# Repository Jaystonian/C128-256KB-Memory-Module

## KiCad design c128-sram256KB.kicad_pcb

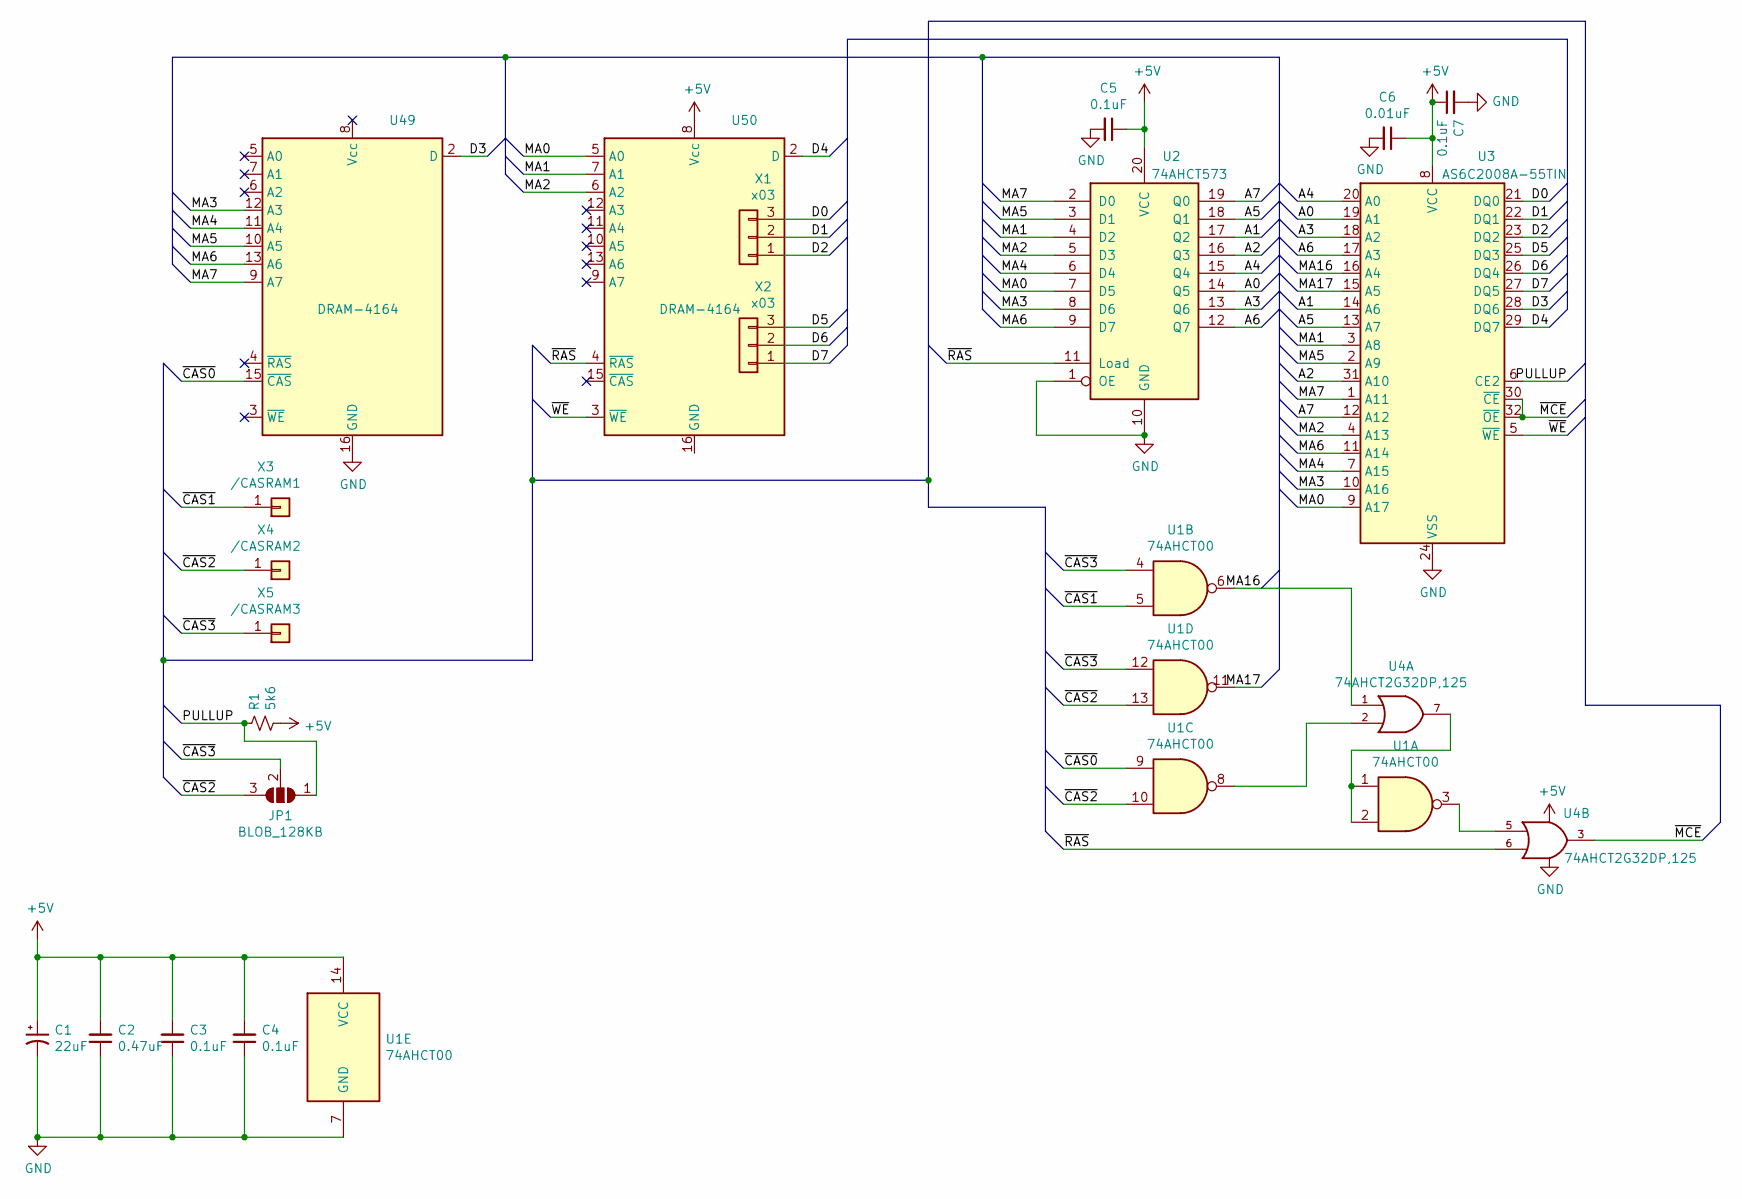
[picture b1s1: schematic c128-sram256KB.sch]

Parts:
C1: 22uF; CP_EIA-6032-28_Kemet-C_Pad2.25x2.35mm_HandSolder
C2: 0.47uF; C_0805_2012Metric_Pad1.15x1.40mm_HandSolder
C3, C4, C5, C7: 0.1uF; C_0805_2012Metric_Pad1.15x1.40mm_HandSolder
C6: 0.01uF; C_0805_2012Metric_Pad1.15x1.40mm_HandSolder
JP1: BLOB_128KB; SolderJumper-3_P2.0mm_Open_TrianglePad1.0x1.5mm
R1: 5k6; R_0805_2012Metric_Pad1.15x1.40mm_HandSolder
U1: 74AHCT00; SOIC-14_3.9x8.7mm_P1.27mm
U2: 74AHCT573; SO-20_12.8x7.5mm_P1.27mm
U3: AS6C2008A-55TIN; TSOP-I-32_11.8x8mm_P0.5mm
U4: 74AHCT2G32DP,125; TSSOP-8_3x3mm_P0.65mm
U49: DRAM-4164; DIP-16_W7.62mm-DRAM4164L
U50: DRAM-4164; DIP-16_W7.62mm-DRAM4164R
X1, X2: x03; PinHeader_1x03_P2.54mm_Vertical
X3: /CASRAM1; PinHeader_1x01_P2.54mm_Vertical
X4: /CASRAM2; PinHeader_1x01_P2.54mm_Vertical
X5: /CASRAM3; PinHeader_1x01_P2.54mm_Vertical

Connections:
+5V: C1.1, C2.2, C3.2, C4.2, C5.1, C6.1, C7.1, R1.2, U1.14 (VCC), U2.20 (VCC), U3.8 (VCC), U4.8 (VCC), U50.8 (Vcc)
/A0: U2.14 (Q5), U3.19 (A1)
/A1: U2.17 (Q2), U3.14 (A6)
/A2: U2.16 (Q3), U3.31 (A10)
/A3: U2.13 (Q6), U3.18 (A2)
/A4: U2.15 (Q4), U3.20 (A0)
/A5: U2.18 (Q1), U3.13 (A7)
/A6: U2.12 (Q7), U3.17 (A3)
/A7: U2.19 (Q0), U3.12 (A12)
/D0: U3.21 (DQ0), X1.3
/D1: U3.22 (DQ1), X1.2
/D2: U3.23 (DQ2), X1.1
/D3: U3.28 (DQ6), U49.2 (D)
/D4: U3.29 (DQ7), U50.2 (D)
/D5: U3.25 (DQ3), X2.3
/D6: U3.26 (DQ4), X2.2
/D7: U3.27 (DQ5), X2.1
/MA0: U2.7 (D5), U3.9 (A17), U50.5 (A0)
/MA1: U2.4 (D2), U3.3 (A8), U50.7 (A1)
/MA2: U2.5 (D3), U3.4 (A13), U50.6 (A2)
/MA3: U2.8 (D6), U3.10 (A16), U49.12 (A3)
/MA4: U2.6 (D4), U3.7 (A15), U49.11 (A4)
/MA5: U2.3 (D1), U3.2 (A9), U49.10 (A5)
/MA6: U2.9 (D7), U3.11 (A14), U49.13 (A6)
/MA7: U2.2 (D0), U3.1 (A11), U49.9 (A7)
/MA16: U1.6, U3.16 (A4), U4.1
/MA17: U1.11, U3.15 (A5)
/PULLUP: JP1.1 (A), R1.1, U3.6 (CE2); also elsewhere on the board
/~CAS0: U1.9, U49.15 (~CAS)
/~CAS1: U1.5, X3.1
/~CAS2: JP1.3 (B), U1.10, U1.13, X4.1; also elsewhere on the board
/~CAS3: JP1.2 (C), U1.4, U1.12, X5.1; also elsewhere on the board
/~MCE: U3.30 (~CE), U3.32 (~OE), U4.3
/~RAS: U2.11 (Load), U4.6, U50.4 (~RAS)
/~WE: U3.5 (~WE), U50.3 (~WE~)
GND: C1.2, C2.1, C3.1, C4.1, C5.2, C6.2, C7.2, U1.7 (GND), U2.1 (OE), U2.10 (GND), U3.24 (VSS), U4.4 (GND), U49.16 (GND)
unnamed: U1.1, U1.2, U4.7
unnamed: U1.3, U4.5
unnamed: U1.8, U4.2

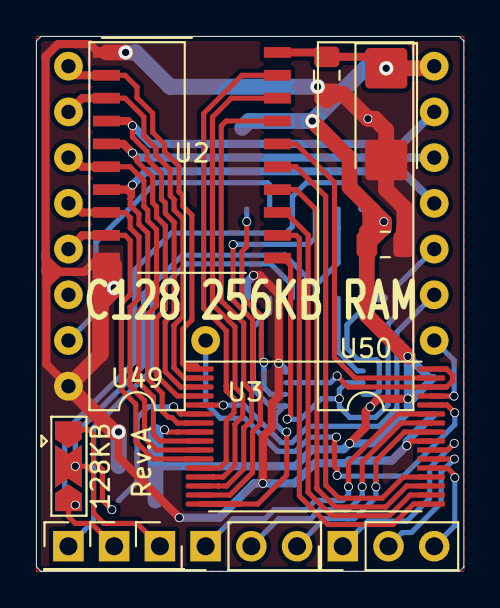
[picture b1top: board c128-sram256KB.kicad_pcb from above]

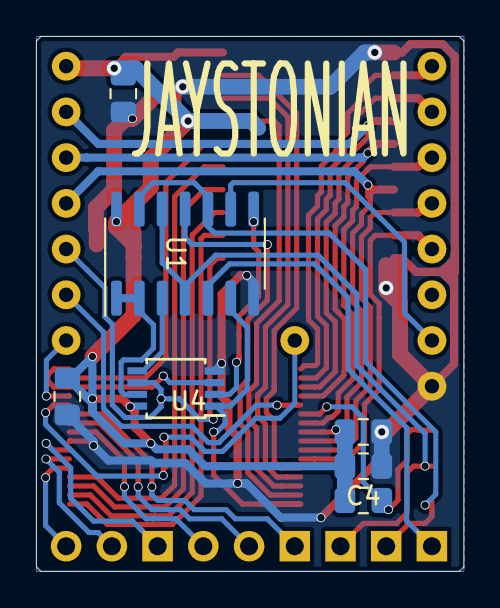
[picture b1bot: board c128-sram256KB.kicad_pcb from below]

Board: 2 copper layers, 23.7 x 29.7 mm, 20 parts (7 on the bottom side), 39 nets.

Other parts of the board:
128KB: BLOB_128KB; SolderJumper-3_P2.0mm_Open_TrianglePad1.0x1.5mm

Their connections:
/PULLUP: 128KB.1; also elsewhere on the board
/~CAS2: 128KB.3; also elsewhere on the board
/~CAS3: 128KB.2; also elsewhere on the board
